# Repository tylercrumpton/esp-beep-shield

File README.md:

# BEEP Shield
Passive piezo buzzer shield for the D1 Mini ESP8266 board.

![pcb-front]![pcb-back]

## Overview
The **BEEP Shield** fits the Wemos D1 Mini ESP8266 development boards and contains a 5V "passive" piezo buzzer.
This allows you to make tones from 2KHz to 5KHz using a single IO pin.

## Operation
The **BEEP Shield** works well with the Arduino `tone()` function, and the pin mappings are as follows:

| Description    | D1 Mini Pin |
|----------------|-------------|
| 5V Supply      | 5V          |
| Ground         | GND         |
| Buzzer Control | D6          |

All other pins are not used and are not connected.

[pcb-front]: https://cloud.githubusercontent.com/assets/1317406/24598057/14bfc128-180f-11e7-8c8c-d3699ac8b2c8.png
[pcb-back]: https://cloud.githubusercontent.com/assets/1317406/24598063/1cf48612-180f-11e7-97a8-c578592f99b6.png

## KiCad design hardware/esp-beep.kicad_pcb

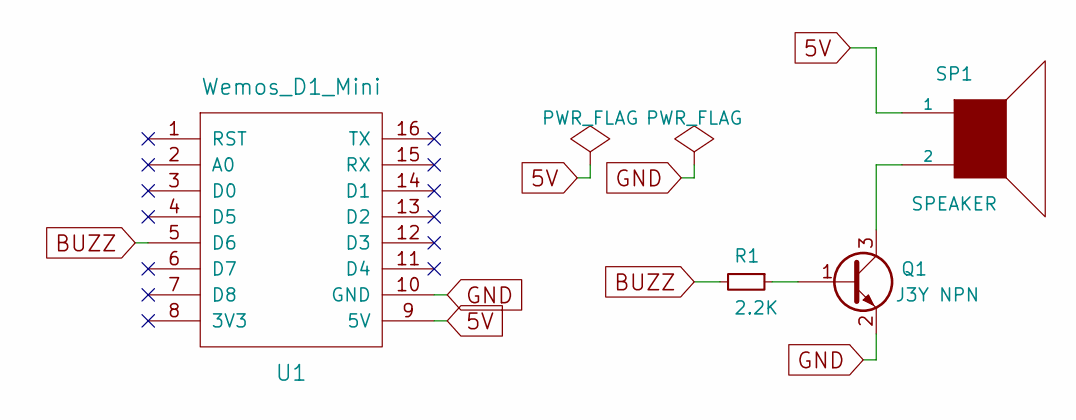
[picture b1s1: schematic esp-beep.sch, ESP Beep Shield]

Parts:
Q1: J3Y NPN; SOT-23_Handsoldering
R1: 2.2K; R_0805_HandSoldering
SP1: SPEAKER; 5V_buzzer
U1: Wemos_D1_Mini; D1_mini

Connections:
5V: SP1.1, U1.9 (5V)
BUZZ: R1.2, U1.5 (D6)
GND: Q1.2 (E), U1.10 (GND)
unnamed: Q1.1 (B), R1.1
unnamed: Q1.3 (C), SP1.2

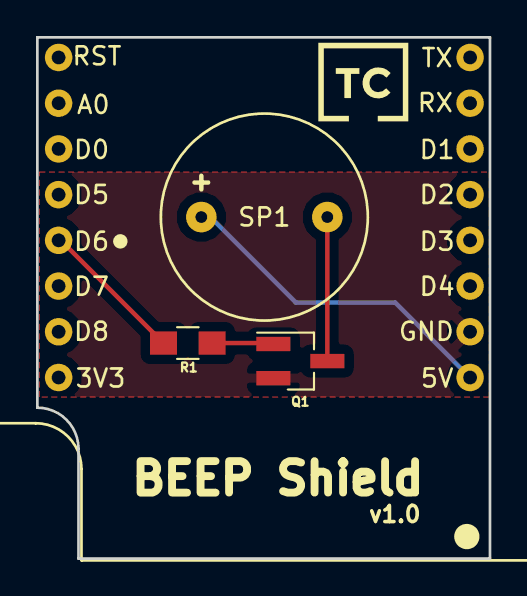
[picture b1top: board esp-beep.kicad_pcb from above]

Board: 2 copper layers, 25.1 x 29.0 mm, 6 parts (1 on the bottom side), 5 nets.

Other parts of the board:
svg2mod, svg2mod#2: G***; tc_30mm

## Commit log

2017-03-30 Initial project setup.
2017-04-03 Update CrumpPrints to include 5V buzzer.
2017-04-03 Capture schematic layout.
2017-04-03 Add empty ProjectSpecific footprint repo.
2017-04-03 Assign footprints to schematic symbols.
2017-04-03 Add PCB layout.
2017-04-03 Add plot settings to PCB.
2017-04-03 Add README.md file.
2017-04-04 Add output directory to gitignore.

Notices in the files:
hardware/esp-beep.kicad_pcb:
CC-BY-SA 4.0
